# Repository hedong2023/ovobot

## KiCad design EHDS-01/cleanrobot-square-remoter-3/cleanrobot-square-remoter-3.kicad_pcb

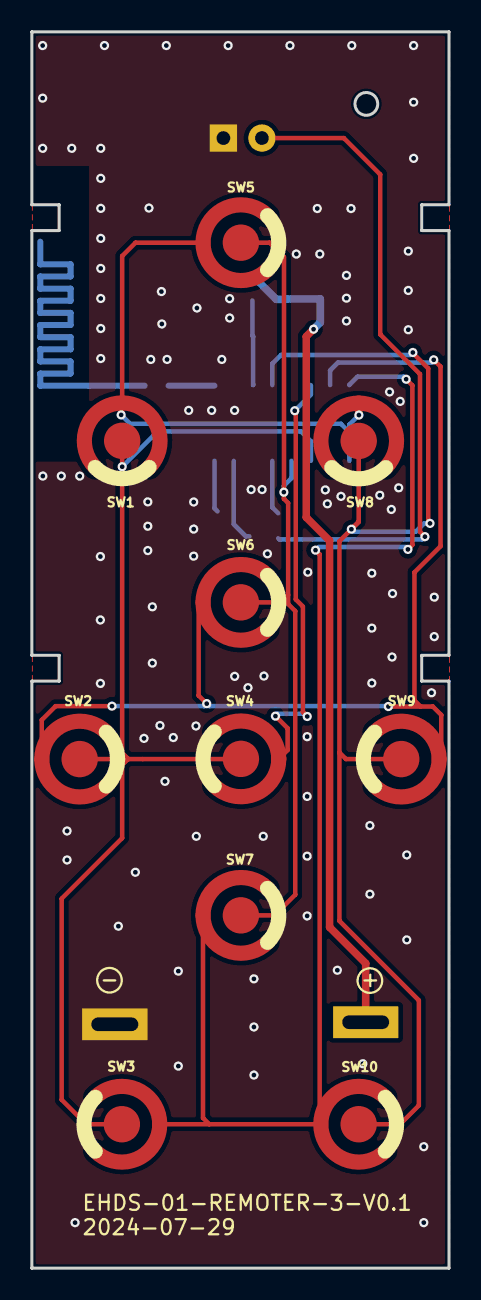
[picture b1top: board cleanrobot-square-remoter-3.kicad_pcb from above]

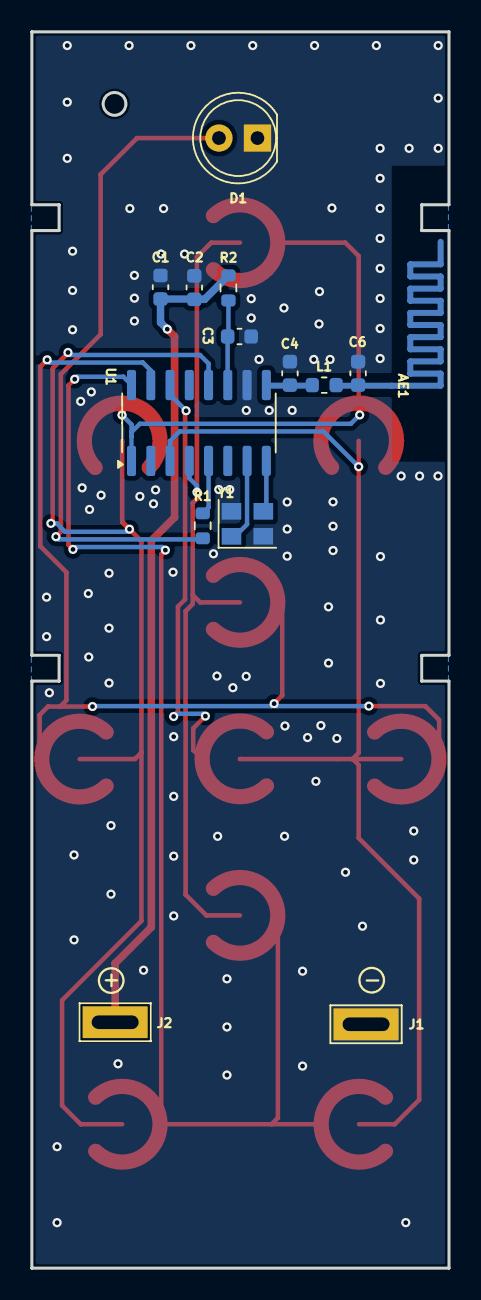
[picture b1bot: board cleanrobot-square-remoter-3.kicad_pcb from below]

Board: 2 copper layers, 27.5 x 81.5 mm, 24 parts (14 on the bottom side), 16 nets.

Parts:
AE1: Antenna_Shield; Ovo_PA2401_2.4GHz_Left
C1: 10uF; C_0603_1608Metric
C2: 100pF; C_0603_1608Metric
C3: 0.1uF; C_0603_1608Metric
C4: 1.2pF; C_0603_1608Metric
C6: 0.5pF; C_0603_1608Metric
D1: RED; LED_D5.0mm
J1: 负极弹簧; Pad_THTPad_4.3x2.1mm_Drill3.1x0.9mm
J2: 正极弹簧; Pad_THTPad_4.3x2.1mm_Drill3.1x0.9mm
L1: 3.3uH; L_0603_1608Metric
R1: 1K; R_0603_1608Metric
R2: 10R; R_0603_1608Metric
SW1, SW2, SW3, SW4, SW5, SW6, SW7, SW8, SW9, SW10: SW; Dome_SLICE_ARC_6x6mm
U1: GH8266-Q; SOP-16_3.9x9.9mm_P1.27mm
Y1: 16MHz/12pF(10ppm); Oscillator_SMD_Abracon_ASE-4Pin_3.2x2.5mm

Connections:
+3V3: C1.1, C2.1, J2.1, R2.1
/H1: SW1.1, SW5.1, SW8.1, U1.1 (PA0)
/H2: SW2.1, SW6.1, SW9.1, U1.15 (PA3)
/H3: SW3.1, SW7.1, SW10.1, U1.16 (PA4)
/H4: SW4.1, U1.14 (PA6)
/V1: SW1.2, SW2.2, SW3.2, SW4.2, U1.3 (PB1)
/V2: SW5.2, SW6.2, SW7.2, U1.4 (PB3)
/V3: SW8.2, SW9.2, SW10.2, U1.12 (PA7)
GND: C1.2, C2.2, C3.2, C4.1, C6.1, D1.1 (K), J1.1, U1.10 (GND), Y1.2, Y1.4
unnamed: AE1.1 (A), C6.2, L1.1
unnamed: D1.2 (A), R1.1
unnamed: R1.2, U1.5 (PB2)
unnamed: C4.2, L1.2, U1.9 (RF-ANT)
unnamed: C3.1, R2.2, U1.11 (VDD)
unnamed: U1.8 (XTALN), Y1.3
unnamed: U1.7 (XTALP), Y1.1

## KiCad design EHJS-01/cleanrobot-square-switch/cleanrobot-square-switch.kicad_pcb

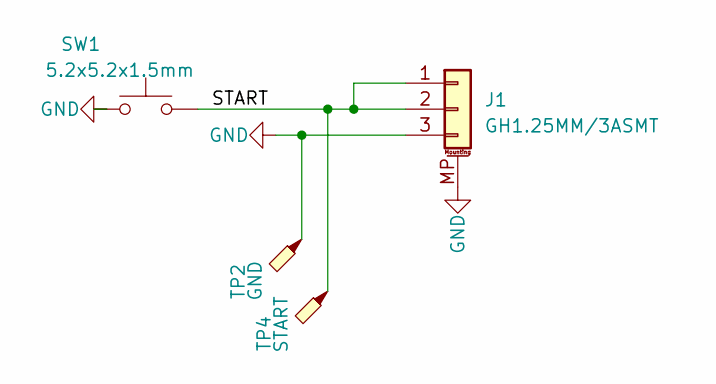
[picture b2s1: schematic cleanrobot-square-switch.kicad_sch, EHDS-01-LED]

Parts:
J1: GH1.25MM/3ASMT; JST_GH_BM03B-GHS-TBT_1x03-1MP_P1.25mm_Vertical
SW1: 5.2x5.2x1.5mm; SW_SPST_TL3342
TP2: GND; TestPoint_Pad_D1.0mm
TP4: START; TestPoint_Pad_D1.0mm

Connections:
/START: J1.1, J1.2, SW1.2, TP4.1
GND: J1.3, J1.MP (MountPin), SW1.1, TP2.1

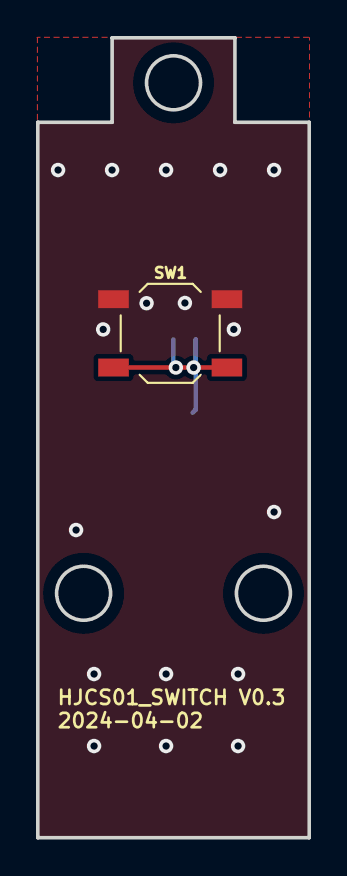
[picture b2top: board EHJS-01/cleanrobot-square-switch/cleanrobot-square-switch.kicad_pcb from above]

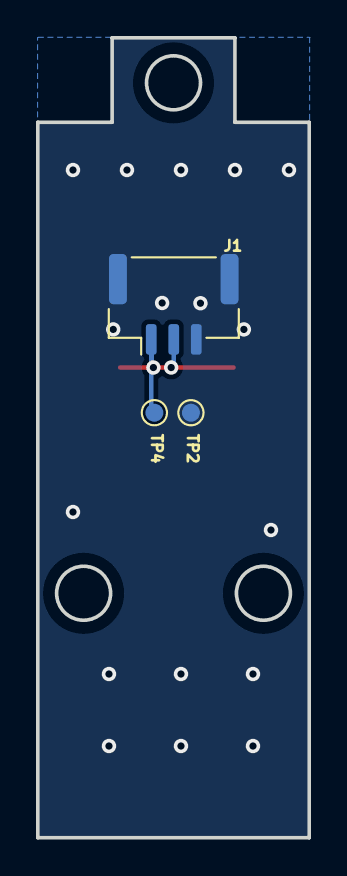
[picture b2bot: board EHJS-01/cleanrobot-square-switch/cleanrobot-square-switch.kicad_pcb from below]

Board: 2 copper layers, 15.1 x 44.4 mm, 4 parts (3 on the bottom side), 2 nets.

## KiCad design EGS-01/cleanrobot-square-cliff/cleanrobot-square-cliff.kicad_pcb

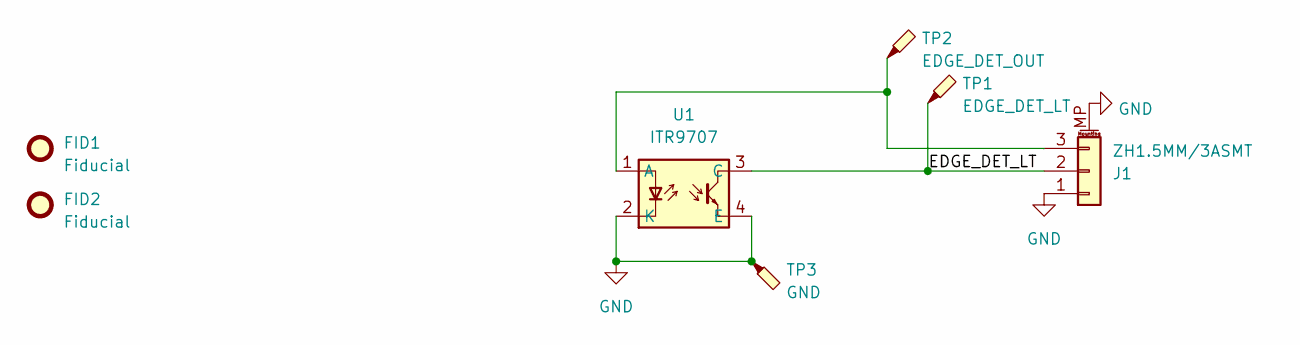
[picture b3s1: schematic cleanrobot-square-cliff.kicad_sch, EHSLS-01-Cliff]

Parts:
FID1, FID2: Fiducial; Fiducial_1mm_Mask2mm
J1: ZH1.5MM/3ASMT; JST_ZH_B3B-ZR-SM4-TF_1x03-1MP_P1.50mm_Vertical
TP1: EDGE_DET_LT; TestPoint_Pad_D1.0mm
TP2: EDGE_DET_OUT; TestPoint_Pad_D1.0mm
TP3: GND; TestPoint_Pad_D1.0mm
U1: ITR9707; EverLight_ITR9707_12.8x6.4mm_P2.54mm

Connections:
/EDGE_DET_LT: J1.2, TP1.1, U1.3 (C)
GND: J1.1, J1.MP (MountPin), TP3.1, U1.2 (K), U1.4 (E)
unnamed: J1.3, TP2.1, U1.1 (A)

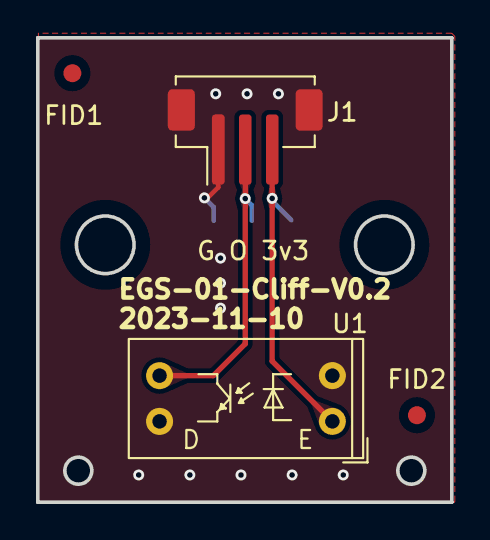
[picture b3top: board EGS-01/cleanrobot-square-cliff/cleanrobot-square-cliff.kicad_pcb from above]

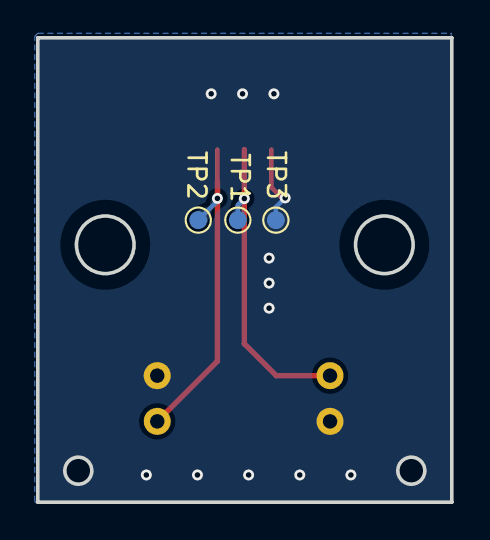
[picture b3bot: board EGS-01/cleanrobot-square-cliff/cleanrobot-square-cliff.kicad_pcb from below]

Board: 2 copper layers, 23.0 x 25.8 mm, 7 parts (3 on the bottom side), 3 nets.

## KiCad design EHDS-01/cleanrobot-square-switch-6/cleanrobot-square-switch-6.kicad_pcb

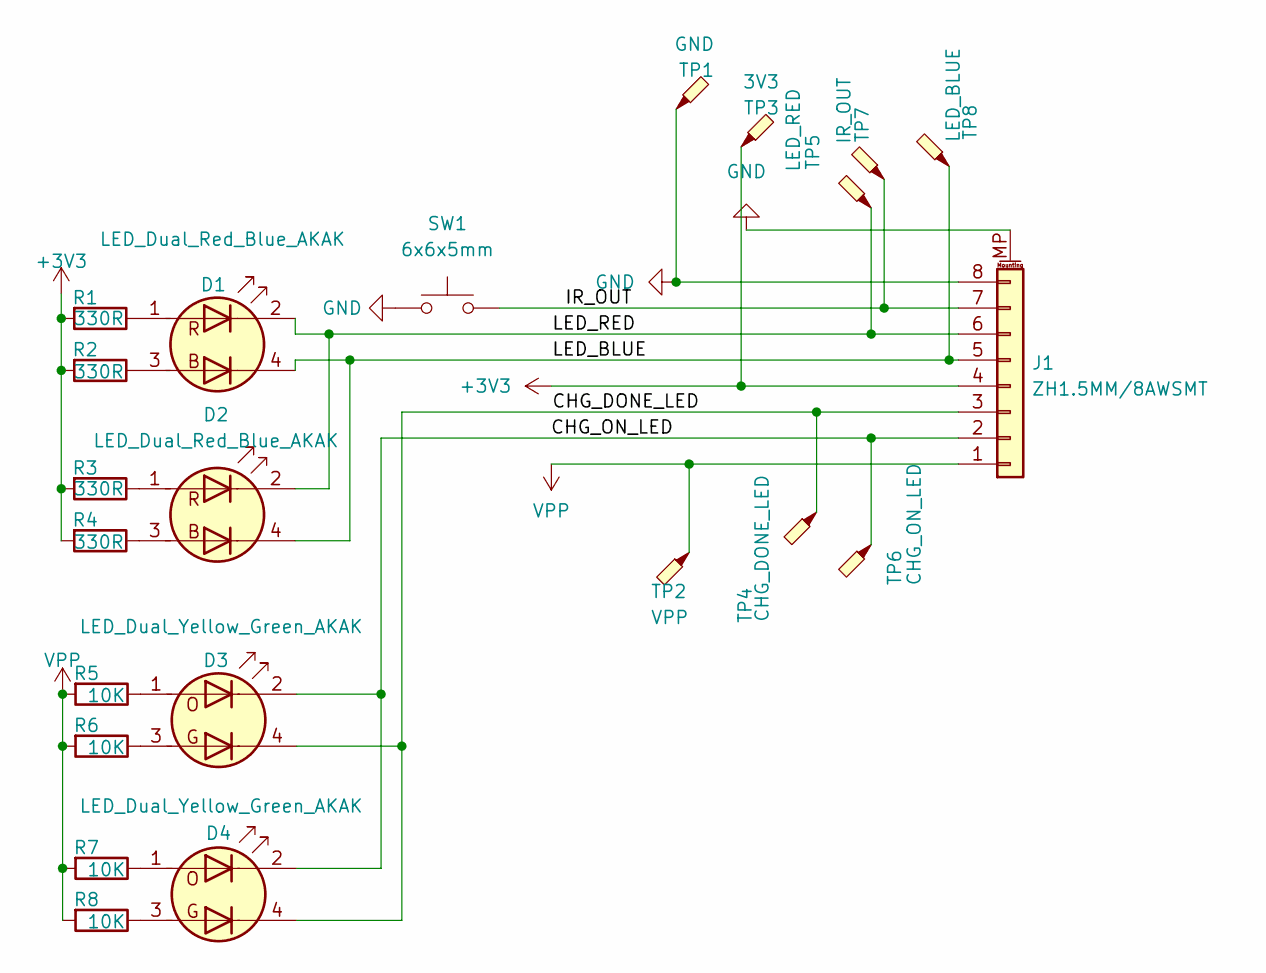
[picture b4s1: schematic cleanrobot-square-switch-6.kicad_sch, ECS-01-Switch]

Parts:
D1, D2: LED_Dual_Red_Blue_AKAK; LED_Dual_1.6x1.5mm
D3, D4: LED_Dual_Yellow_Green_AKAK; LED_Dual_1.6x1.5mm
J1: ZH1.5MM/8AWSMT; JST_ZH_S8B-ZR-SM4-TF_1x08-1MP_P1.50mm_Horizontal
R1, R2, R3, R4: 330R; R_0603_1608Metric
R5, R6, R7, R8: 10K; R_0603_1608Metric
SW1: 6x6x5mm; SW_Push_1P1T_NO_6x6mm_H5.0mm
TP1: GND; TestPoint_Pad_D1.0mm
TP2: VPP; TestPoint_Pad_D1.0mm
TP3: 3V3; TestPoint_Pad_D1.0mm
TP4: CHG_DONE_LED; TestPoint_Pad_D1.0mm
TP5: LED_RED; TestPoint_Pad_D1.0mm
TP6: CHG_ON_LED; TestPoint_Pad_D1.0mm
TP7: IR_OUT; TestPoint_Pad_D1.0mm
TP8: LED_BLUE; TestPoint_Pad_D1.0mm

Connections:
+3V3: J1.4, R1.2, R2.2, R3.2, R4.2, TP3.1
/CHG_DONE_LED: D3.4 (K2), D4.4 (K2), J1.3, TP4.1
/CHG_ON_LED: D3.2 (K1), D4.2 (K1), J1.2, TP6.1
/IR_OUT: J1.7, SW1.2, TP7.1
/LED_BLUE: D1.4 (K2), D2.4 (K2), J1.5, TP8.1
/LED_RED: D1.2 (K1), D2.2 (K1), J1.6, TP5.1
GND: J1.8, J1.MP (MountPin), SW1.1, TP1.1
unnamed: D1.1 (A1), R1.1
unnamed: D1.3 (A2), R2.1
unnamed: D2.1 (A1), R3.1
unnamed: D2.3 (A2), R4.1
unnamed: D3.1 (A1), R5.1
unnamed: D3.3 (A2), R6.1
unnamed: D4.1 (A1), R7.1
unnamed: D4.3 (A2), R8.1
VPP: J1.1, R5.2, R6.2, R7.2, R8.2, TP2.1

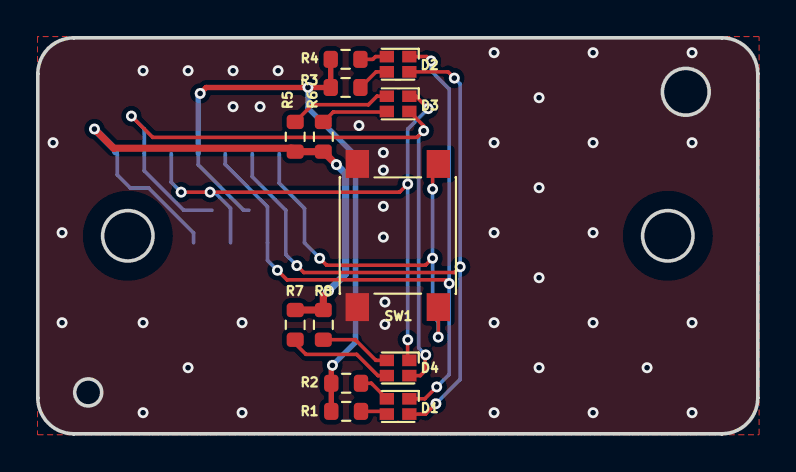
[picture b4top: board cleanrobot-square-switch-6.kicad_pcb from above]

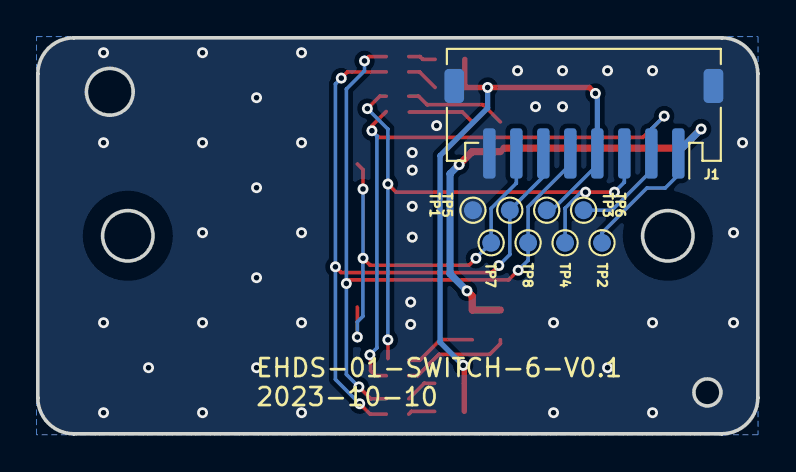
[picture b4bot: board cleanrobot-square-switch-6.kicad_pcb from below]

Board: 2 copper layers, 40.0 x 22.0 mm, 22 parts (9 on the bottom side), 16 nets.

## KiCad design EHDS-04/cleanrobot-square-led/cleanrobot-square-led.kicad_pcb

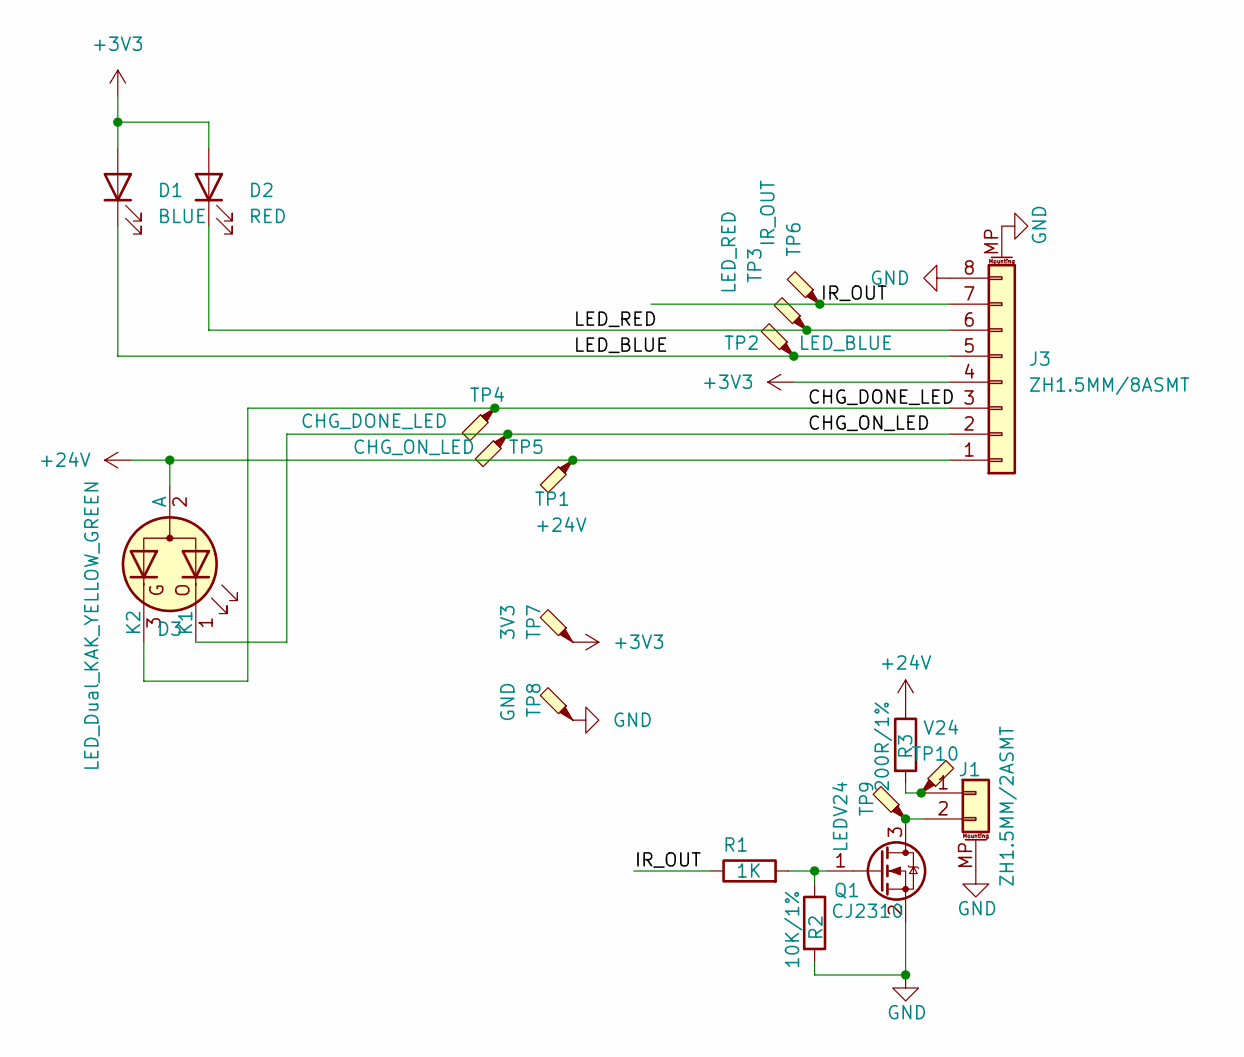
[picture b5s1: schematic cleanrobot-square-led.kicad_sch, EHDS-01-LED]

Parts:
D1: BLUE; LED_0603_1608Metric
D2: RED; LED_0603_1608Metric
D3: LED_Dual_KAK_YELLOW_GREEN; LED_Dual_1.6x1.5mm
J1: ZH1.5MM/2ASMT; JST_ZH_B2B-ZR-SM4-TF_1x02-1MP_P1.50mm_Vertical
J3: ZH1.5MM/8ASMT; JST_ZH_B8B-ZR-SM4-TF_1x08-1MP_P1.50mm_Vertical
Q1: CJ2310; SOT-23
R1: 1K; R_0603_1608Metric
R2: 10K/1%; R_0603_1608Metric
R3: 200R/1%; R_0805_2012Metric
TP1: +24V; TestPoint_Pad_D1.0mm
TP2: LED_BLUE; TestPoint_Pad_D1.0mm
TP3: LED_RED; TestPoint_Pad_D1.0mm
TP4: CHG_DONE_LED; TestPoint_Pad_D1.0mm
TP5: CHG_ON_LED; TestPoint_Pad_D1.0mm
TP6: IR_OUT; TestPoint_Pad_D1.0mm
TP7: 3V3; TestPoint_Pad_D1.0mm
TP8: GND; TestPoint_Pad_D1.0mm
TP9: LEDV24; TestPoint_Pad_D1.0mm
TP10: V24; TestPoint_Pad_D1.0mm

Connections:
+3V3: D1.2 (A), D2.2 (A), J3.4, TP7.1
+24V: D3.2 (A), J3.1, R3.1, TP1.1
/CHG_DONE_LED: D3.3 (K2), J3.3, TP4.1
/CHG_ON_LED: D3.1 (K1), J3.2, TP5.1
/IR_OUT: J3.7, R1.1, TP6.1
/LED_BLUE: D1.1 (K), J3.5, TP2.1
/LED_RED: D2.1 (K), J3.6, TP3.1
GND: J1.MP (MountPin), J3.8, J3.MP (MountPin), Q1.2 (S), R2.2, TP8.1
unnamed: J1.1, R3.2, TP10.1
unnamed: J1.2, Q1.3 (D), TP9.1
unnamed: Q1.1 (G), R1.2, R2.1

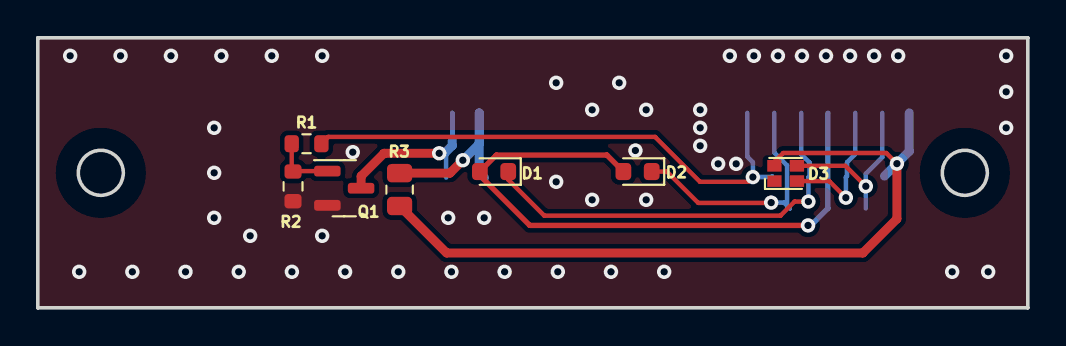
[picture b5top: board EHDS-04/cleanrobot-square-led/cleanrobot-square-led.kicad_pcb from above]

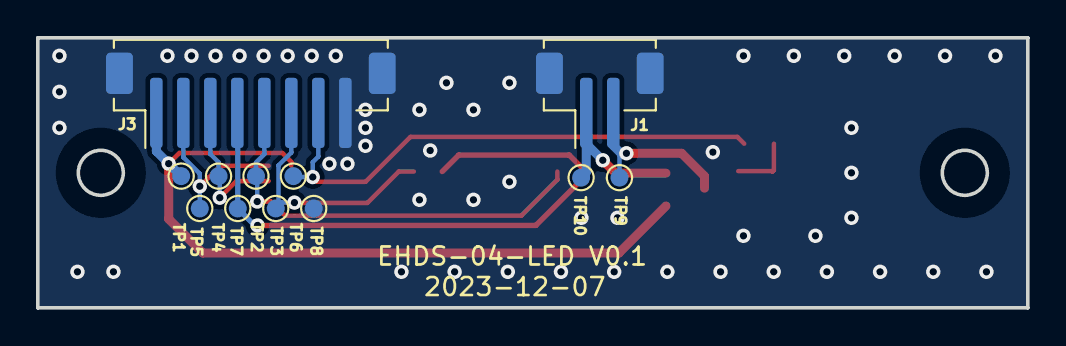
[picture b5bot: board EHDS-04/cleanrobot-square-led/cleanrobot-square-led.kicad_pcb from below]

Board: 2 copper layers, 55.0 x 15.0 mm, 19 parts (12 on the bottom side), 11 nets.

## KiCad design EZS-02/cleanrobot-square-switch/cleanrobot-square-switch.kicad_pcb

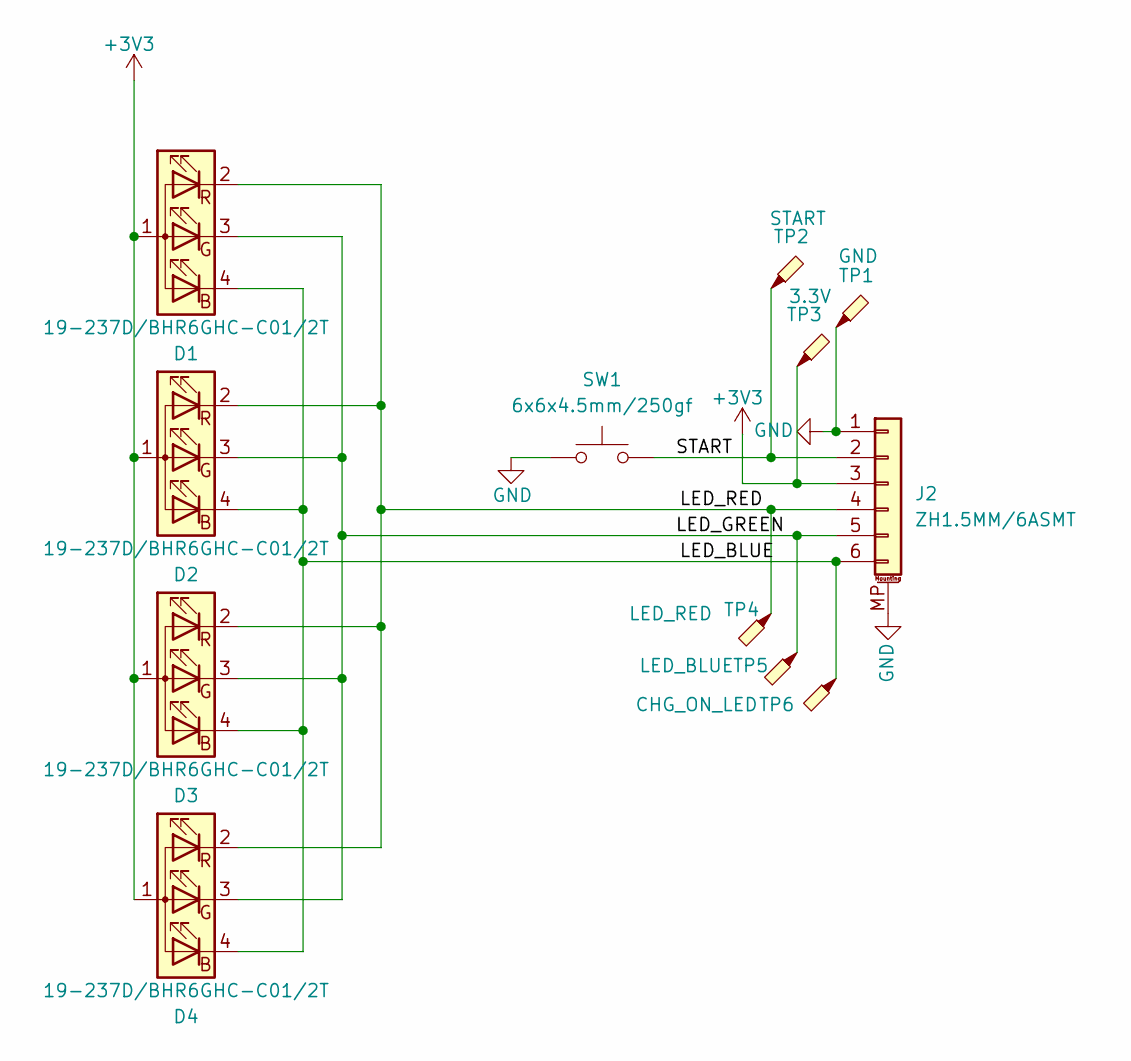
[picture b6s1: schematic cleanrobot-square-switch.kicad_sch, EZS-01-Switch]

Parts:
D1, D2, D3, D4: 19-237D/BHR6GHC-C01/2T; LED_Everlight_ARGB_1.6x1.6mm
J2: ZH1.5MM/6ASMT; JST_ZH_B6B-ZR-SM4-TF_1x06-1MP_P1.50mm_Vertical
SW1: 6x6x4.5mm/250gf; SW_Push_1P1T_NO_6x6mm_H4.5mm
TP1: GND; TestPoint_Pad_D1.0mm
TP2: START; TestPoint_Pad_D1.0mm
TP3: 3.3V; TestPoint_Pad_D1.0mm
TP4: LED_RED; TestPoint_Pad_D1.0mm
TP5: LED_BLUE; TestPoint_Pad_D1.0mm
TP6: CHG_ON_LED; TestPoint_Pad_D1.0mm

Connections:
+3V3: D1.1 (A), D2.1 (A), D3.1 (A), D4.1 (A), J2.3, TP3.1
/LED_BLUE: D1.4 (BK), D2.4 (BK), D3.4 (BK), D4.4 (BK), J2.6, TP6.1
/LED_GREEN: D1.3 (GK), D2.3 (GK), D3.3 (GK), D4.3 (GK), J2.5, TP5.1
/LED_RED: D1.2 (RK), D2.2 (RK), D3.2 (RK), D4.2 (RK), J2.4, TP4.1
/START: J2.2, SW1.2, TP2.1
GND: J2.1, J2.MP (MountPin), SW1.1, TP1.1

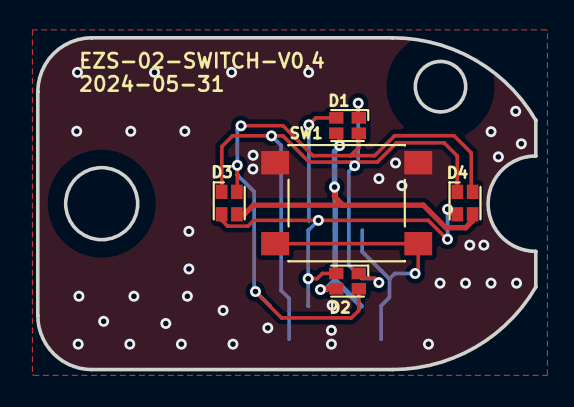
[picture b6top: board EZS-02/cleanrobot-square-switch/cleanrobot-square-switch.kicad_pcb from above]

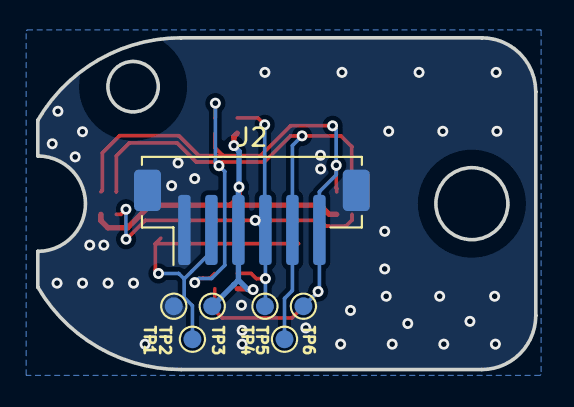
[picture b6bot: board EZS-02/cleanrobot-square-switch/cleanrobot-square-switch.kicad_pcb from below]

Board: 2 copper layers, 27.7 x 18.4 mm, 12 parts (7 on the bottom side), 6 nets.

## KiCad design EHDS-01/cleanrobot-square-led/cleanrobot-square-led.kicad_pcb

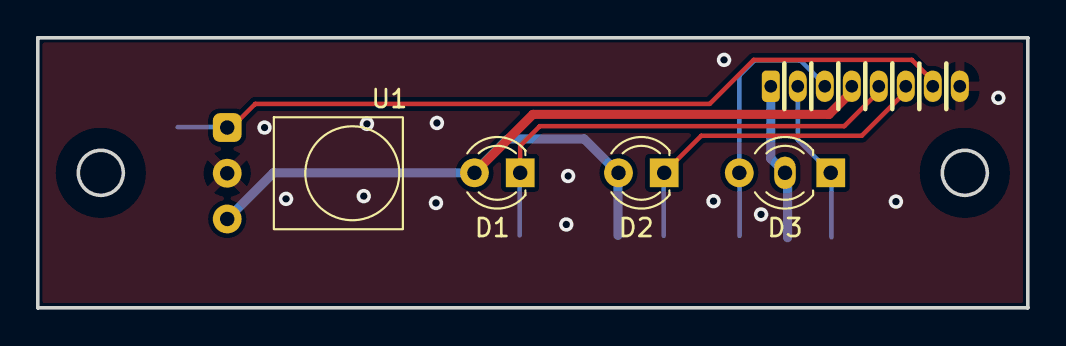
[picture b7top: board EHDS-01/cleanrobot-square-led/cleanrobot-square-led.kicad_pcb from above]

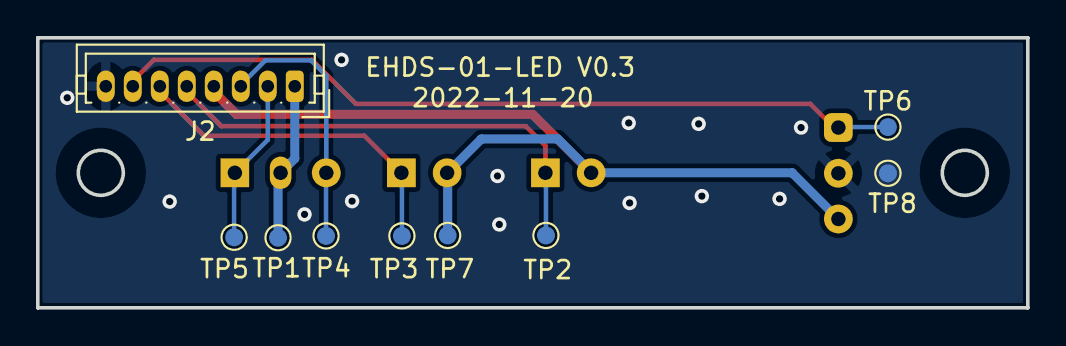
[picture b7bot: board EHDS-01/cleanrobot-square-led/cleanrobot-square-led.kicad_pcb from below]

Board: 2 copper layers, 55.0 x 15.0 mm, 13 parts (9 on the bottom side), 8 nets.

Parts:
D1: BLUE; LED_D3.0mm
D2: RED; LED_D3.0mm
D3: LED_Dual_KAK_YELLOW_GREEN; LED_D3.0mm-3
J2: ZH1.5MM/8A; JST_ZH_B08B-ZR_1x08_P1.50mm_Vertical
TP1: +24V; TestPoint_Pad_D1.0mm
TP2: LED_BLUE; TestPoint_Pad_D1.0mm
TP3: LED_RED; TestPoint_Pad_D1.0mm
TP4: CHG_DONE_LED; TestPoint_Pad_D1.0mm
TP5: CHG_ON_LED; TestPoint_Pad_D1.0mm
TP6: IR_OUT; TestPoint_Pad_D1.0mm
TP7: 3V3; TestPoint_Pad_D1.0mm
TP8: GND; TestPoint_Pad_D1.0mm
U1: NC/IRM-3640CF45; Everlight_IRM-3640CF45

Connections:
+3V3: D1.2 (A), D2.2 (A), J2.4, TP7.1, U1.3 (Vs)
+24V: D3.2 (A), J2.1, TP1.1
/CHG_DONE_LED: D3.3 (K2), J2.3, TP4.1
/CHG_ON_LED: D3.1 (K1), J2.2, TP5.1
/IR_OUT: J2.7, TP6.1, U1.1 (OUT)
/LED_BLUE: D1.1 (K), J2.5, TP2.1
/LED_RED: D2.1 (K), J2.6, TP3.1
GND: J2.8, TP8.1, U1.2 (GND)

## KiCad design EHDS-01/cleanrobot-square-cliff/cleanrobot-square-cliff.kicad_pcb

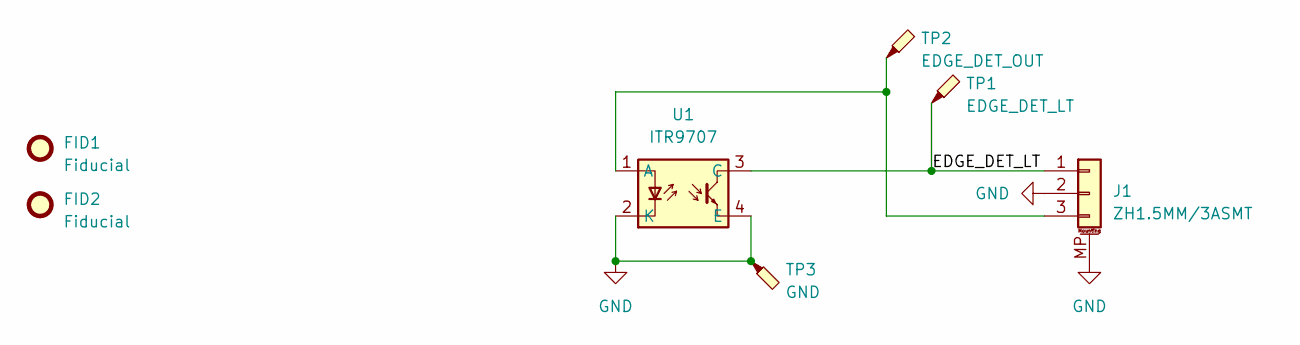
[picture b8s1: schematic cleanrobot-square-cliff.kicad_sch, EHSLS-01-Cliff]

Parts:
FID1, FID2: Fiducial; Fiducial_1mm_Mask2mm
J1: ZH1.5MM/3ASMT; JST_ZH_B3B-ZR-SM4-TF_1x03-1MP_P1.50mm_Vertical
TP1: EDGE_DET_LT; TestPoint_Pad_D1.0mm
TP2: EDGE_DET_OUT; TestPoint_Pad_D1.0mm
TP3: GND; TestPoint_Pad_D1.0mm
U1: ITR9707; EverLight_ITR9707_12.8x6.4mm_P2.54mm

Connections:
/EDGE_DET_LT: J1.1, TP1.1, U1.3 (C)
GND: J1.2, J1.MP (MountPin), TP3.1, U1.2 (K), U1.4 (E)
unnamed: J1.3, TP2.1, U1.1 (A)
